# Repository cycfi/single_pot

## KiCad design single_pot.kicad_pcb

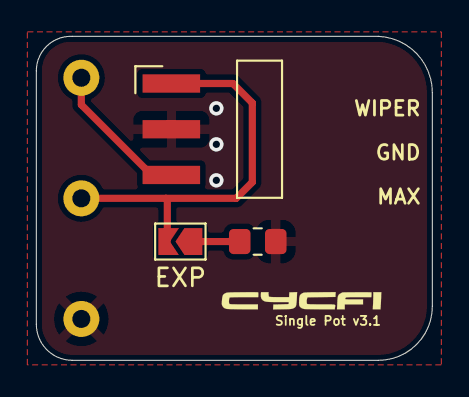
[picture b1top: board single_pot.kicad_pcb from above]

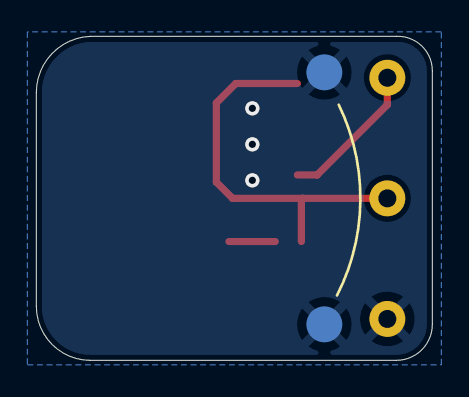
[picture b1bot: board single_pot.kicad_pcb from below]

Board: 2 copper layers, 22.0 x 18.0 mm, 6 parts (2 on the bottom side), 4 nets.

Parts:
H1, H2: Ground Pad; single-pad-2x2-circular
J1: I/O connector; pin_header_1x3p_2.54mm_smd_horizontal
JP1: SolderJumper_2_Open; SolderJumper-2_P1.3mm_Open_TrianglePad1.0x1.5mm
R1: 100k; R_0805_2012Metric_Pad1.20x1.40mm_HandSolder
RV1: 500k; bourns_pdb241

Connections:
GND: H1.1, H2.1, J1.2, R1.1, RV1.3
MAX: J1.3, RV1.1
unnamed: JP1.1 (A), R1.2
WIPER: J1.1, JP1.2 (B), RV1.2

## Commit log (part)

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2022-06-23 Added single (big) pot
2023-01-22 Added fab and updates
2023-08-05 Added taper resistor
